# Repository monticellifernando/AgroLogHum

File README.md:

# AgroLogHum
Repositorio con codigo y diseño de AgroLogHum

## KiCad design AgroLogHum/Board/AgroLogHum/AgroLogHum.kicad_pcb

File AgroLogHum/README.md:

# AgroLogHum v2.0

## Hardware:

| Hw                                                                                            | Tipo           |
| ----                                                                                          | -----          |
| Arduino nano                                                                                  | Motherboard    |
| [RTC DS1307](https://naylampmechatronics.com/blog/52_tutorial-rtc-ds1307-y-eeprom-at24c.html) | RTC            |
| LCD 1602                                                                                      | Pantalla       |
| [AHT10](https://learn.adafruit.com/adafruit-aht20/arduino)                                    | Sensor Humedad |

## Conecciones

| Display | Arduino |
| --- | --- |
| rs  | D3  |
| en  | D2  |
| d4  | D4  |
| d5  | D5  |
| d6  | D6  |
| d7  | D7  |

| RTC | AHT10 | Arduino |
| --- | --- |  --- | 
| SCL | SCL | A5 |
| SDA | SDA | A4 |

| SDCard | Arduino |
| ---    | ---     |
| CS     | D10     |
| MOSI   | D11     |
| MISO   | D12     |
| SCK    | D13     |

## Comandos

El dispositivo se comanda desde el puerto serie, via usb a 115200 baud. Los comandos permiten configurar el dispositivo y operarlo. 
| Instrucción | Argumento                       | Detalle                                                                             |
| ------      | ------                          | -----                                                                               |
| B           |                                 | Borra el archivo con todos los registros.                                           |
| CH          | Horas                           | Graba una medición cada <Horas> horas en el archivo de registro                     |
| CM          | Minutos                         | Graba una medición cada <Minutos> minutos en el archivo de registro                 |
| F           | Año,Mes,Día,Hora,Minuto,Segundo | Pone fecha en el dispositivo                                                        |
| G           |                                 | Hace una enrada en el archivo de registro con la fecha y las mediciones del momento |
| L           |                                 | Muestra los datos registrados en el archivo de registro                             |

Si el comando ingresado es incorrecto, el programa va a mosrar un mensaje de ayuda comentando cuales son los comandos posibles.

```
No entendi eso :-P
Comandos posibles:
B -> Borra la memoria
CH <Horas> -> Graba cada <Horas> horas
F <Año>,<Mes>,<Día>,<Hora>,<Minuto>,<Segundo> -> Pone fecha
G -> Graba datos
L -> muestra datos
```

Los comandos se envían por el puerto serie terminados por un fin de linea (o `[ENTER]`). Hay dos tipos de comandos.
* Comandos que consisten en una instrucción
* Comandos que están compuestos por una instrucción y un argumento

Los argumentos se envían separados por un espacio de las Instrucciones. Por ejemplo, para poner la fecha:

    F 2022,6,24,18,3,10
    
Pone la fecha en 24 de junio de 2022 a las 18:03:10. Si el comando fecha `F` es enviado sin argumentos, el dispositivo muestra la fecha actual con el estado de la medición de Humedad y Temperatura

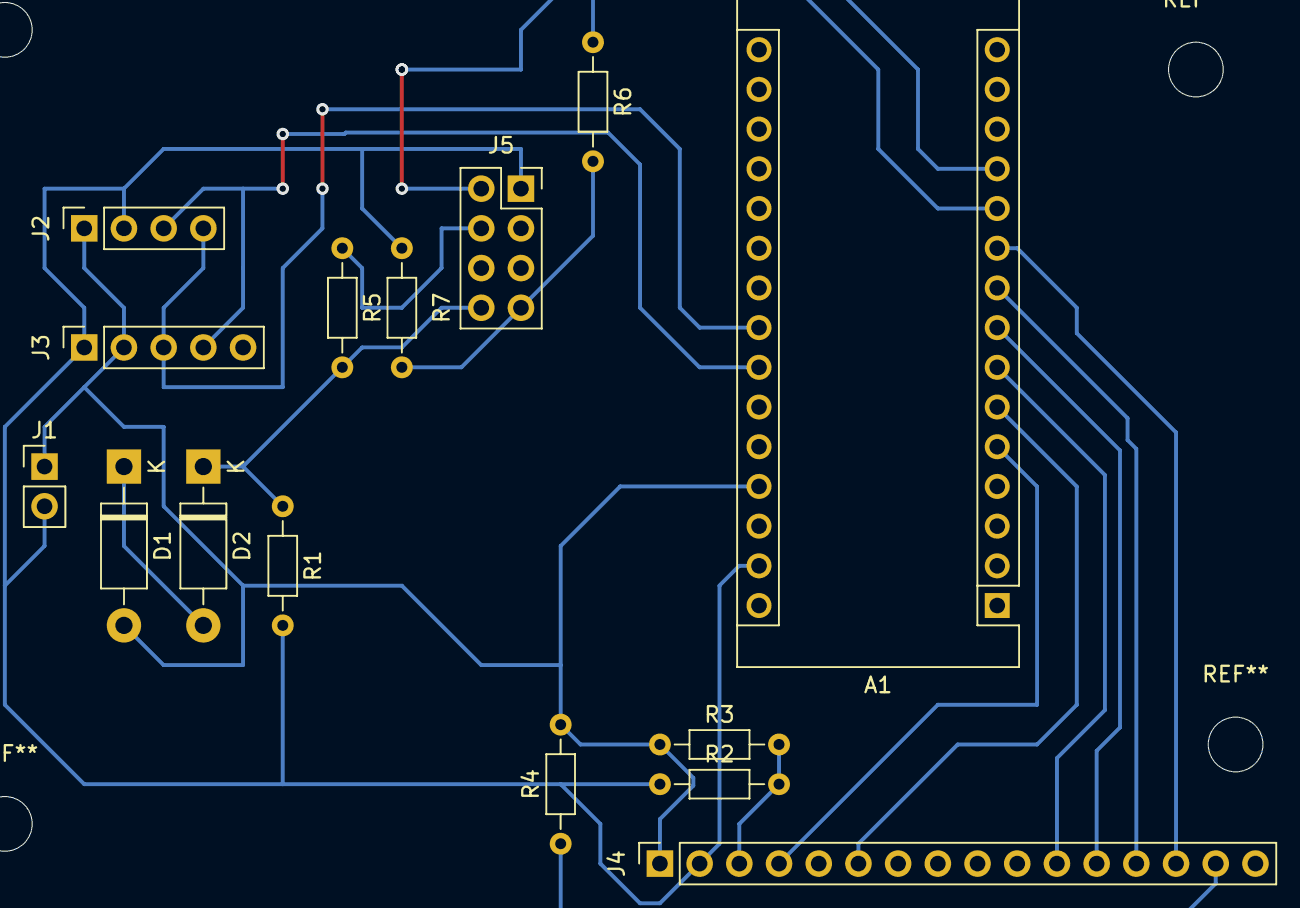
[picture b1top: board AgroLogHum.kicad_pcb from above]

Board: 2 copper layers, 15 parts (0 on the bottom side), 18 nets.

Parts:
A1: Arduino_Nano_v3.x; Arduino_Nano
D1, D2: 1N4007; D_DO-41_SOD81_P10.16mm_Horizontal
J1: Alimentación; PinHeader_1x02_P2.54mm_Vertical
J2: ATH10; PinSocket_1x04_P2.54mm_Vertical
J3: DS 1307; PinSocket_1x05_P2.54mm_Vertical
J4: HD1602; PinSocket_1x16_P2.54mm_Vertical
J5: esp6266; PinSocket_2x04_P2.54mm_Vertical
R1, R5: 10k; R_Axial_DIN0204_L3.6mm_D1.6mm_P7.62mm_Horizontal
R2, R3, R6: 1k; R_Axial_DIN0204_L3.6mm_D1.6mm_P7.62mm_Horizontal
R4: 680; R_Axial_DIN0204_L3.6mm_D1.6mm_P7.62mm_Horizontal
R7: 2k; R_Axial_DIN0204_L3.6mm_D1.6mm_P7.62mm_Horizontal

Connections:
+3V3: D2.1 (K), J5.8 (3.3V), R1.1, R5.2
+5V: A1.27 (+5V), D1.2 (A), J1.1 (In), J2.1 (VIN), J3.2, J4.1 (Vss), R3.1, R4.2
GND: A1.29 (GND), J1.2 (Ext), J2.2 (GND), J3.1, J4.2 (VDD), J4.16 (K), J5.1 (GND), R1.2, R2.1, R7.1
unnamed: A1.5 (D2), J4.4 (RS)
unnamed: A1.6 (D3), J4.6 (E)
unnamed: A1.11 (D8), R6.1
unnamed: A1.12 (D9), J5.2 (TX)
unnamed: A1.23 (A4), J2.4 (SDA), J3.3
unnamed: A1.24 (A5), J2.3 (SCL), J3.4
unnamed: D1.1 (K), D2.2 (A)
unnamed: J4.3 (V0), R2.2, R3.2
unnamed: A1.7 (D4), J4.11 (D4)
unnamed: A1.8 (D5), J4.12 (D5)
unnamed: A1.9 (D6), J4.13 (D6)
unnamed: A1.10 (D7), J4.14 (D7)
unnamed: J4.15 (A), R4.1
unnamed: J5.4 (EN), R5.1
unnamed: J5.7 (RX), R6.2, R7.2

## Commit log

2022-06-17 Adding SD
2022-06-26 Case moved
2022-06-26 VixedMakefile
2022-06-26 fat16
2022-06-26 remofed submopdule fat16
2022-06-26 SD in y funcionando
2022-06-26 def DEBUG
2022-06-26 debug as int flag
2022-06-27 SD working
2022-06-27 Added Binaries
2022-06-27 Case
